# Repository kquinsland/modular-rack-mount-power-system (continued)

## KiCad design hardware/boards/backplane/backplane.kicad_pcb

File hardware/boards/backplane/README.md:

# Consolidated backplane

This directory contains the finalized Generation-2 backplane:
`backplane.kicad_pro`, `backplane.kicad_sch`, `backplane.kicad_pcb`, and
`backplane.kicad_dru`.

The PCB in this directory is the mechanical authority for the board
outline, airflow cutouts, mounting holes, and six slot-connector footprints and
placement. The carrier is the electrical authority for circuitry shared between
the two boards, including the slot pinout, STM32, CAN transceiver, current
sensor, and slot connector pinout.

## Implemented schematic

The root schematic is divided into five sheets:

- `01_power_input.kicad_sch`: DC input, 1 mOhm high-side current shunt,
  INA237 monitor;
- `02_control.kicad_sch`: STM32C092GCU6, reset/decoupling, SWD, and test points;
- `03_can_slots.kicad_sch`: TCAN3413 CAN-FD interface, external CAN protection,
  optional termination, and the six carrier slots;
- `04_fan_status.kicad_sch`: two independent 3-wire fan supply-PWM switches and
  tachometer inputs, plus an externally powered DS18B20 interface. Per-slot
  addressable LEDs were removed to keep automated assembly on one side of the
  PCB; and
- `05_buck_converters.kicad_sch`: separate LM5164 3.3 V and 12 V converters.

The Rust `backplane-firmware` target implements this board. Earlier firmware
targets and their hardware assumptions are not supported.

Both regulators use LM5164DDAR, LCSC C477928, with
PSPMAA0805-101M-ANP 100 uH inductors, LCSC C2962892. The output-specific
feedback, on-time, ripple-injection, and capacitor networks remain separate.

The PCB stackup specifies 2 oz outer copper, 1 oz inner copper, and an ENIG
surface finish.

Generate the backplane BOM, placement file, Gerber/drill archive, IPC-D-356
netlist, designator inventory, and validation manifest with
`mise run production:backplane`. A successful export records warnings in the
manifest; it does not by itself supersede the fabrication-readiness status
below.

The local I2C2 bus uses STM32 PA6/PA7 and exists only between the STM32 and
INA237. Carrier communication is CAN-FD.

## Connectors

`J8` is the main DC input:

1. GND
2. VIN_RAW

`J7` is a XINLAIYA XY308-2.54-3P three-position screw terminal, LCSC
`C557686`:

1. GND
2. CANL
3. CANH

`J7` is intentionally marked DNP and excluded from pick-and-place output because
the user installs it by hand after assembly. D1 and L3 protect only this external
CAN boundary. Each carrier has its own connector-side CAN protection, so the
backplane does not duplicate ESD parts at every slot. `SJ1` and `R17` provide
normally-open 120 ohm termination for use only when this backplane is at a
physical bus end.

`J8` is likewise marked DNP and excluded from pick-and-place output for hand
installation after assembly.

The six carrier slots retain the authoritative combined XT30 plus two-signal
footprint. Their physical pinout is:

1. VIN_BUS — power contact furthest from the two low-voltage signal contacts
2. GND — power contact between pin 1 and the two low-voltage signal contacts
3. CANH
4. CANL

The slot references are `J1` through `J6`, from slot 1 through slot 6. `J9` and
`J11` are independently controlled 3-wire fan connections: GND, switched 12 V,
and tach.

CAN differential nets use KiCad's `_P`/`_N` naming convention on both sides of
the common-mode choke: `CAN_BUS_P`/`CAN_BUS_N` and
`CAN_EXT_P`/`CAN_EXT_N`, with `P = CANH` and `N = CANL`. Custom DRC rules
enforce a 0.20-0.30 mm gap on coupled routes and a 35 mm maximum uncoupled
length. Narrowly scoped breakout areas permit up to 2.40 mm pair spacing at
connector, choke, and transceiver fan-outs. Whole-net skew is intentionally not
constrained because the six-drop `CAN_BUS` trunk is branched; aggregate P/N net
lengths do not describe a meaningful point-to-point signal path.

`J12` is the externally powered DS18B20 header:

1. GND
2. DQ (`DS18B20_DATA`, pulled up to 3.3 V through `R24`)
3. +3V3

The DS18B20 data signal uses STM32 `PA15`. The local status NeoPixel uses `PA1`
through a 100 ohm series resistor and has a dedicated 100 nF bypass capacitor.
Fan 0 uses `PA2` for supply PWM and `PB8` for tach capture. Fan 1 uses `PA0` for
supply PWM and `PA8` for tach capture.

## Power assumptions

The backplane is designed for a **24–48 V nominal system**, compatible with
24 V and future 48 V carrier generations. The current SW3538 carrier is the
limiting factor: **24 V nominal, 30 V maximum input**. A second-generation
carrier with a suitably rated module and protection is required for 48 V use.
Slot feeds are unswitched and do not provide voltage conversion; never connect
a 48 V supply while any current-generation carrier is fitted. No nominal
backplane voltage below 24 V is specified. Supply tolerance, harness drop,
startup, fault protection, and thermal performance remain qualification items.

The first population targets a nominal 24 V input and up to 100 W output per
slot. Six fully loaded slots produce a working input budget of approximately
30 A. `RSH1` is 1 mOhm, giving 30 mV and 0.9 W at 30 A; configure the INA237 for
its narrow shunt range and route the sense pair as true Kelvin connections.

The later design goal is 48 V nominal with a new carrier revision and up to
240 W per slot.
That is a future characterization target, not a released rating, until the
input-protection, current-path, thermal, transient, and first-article tests are
complete.

Both fan channels share the LM5164 12 V rail. Its combined continuous,
startup, and stall load must be tested with the intended pair of fans; adding a
second connector does not increase the regulator's 1 A output rating.

## PCB status

The schematic is synchronized into a fully placed and routed PCB. The finalized
design passes ERC and PCB DRC. Its operating limits remain conditional on the
first-article validation below.

Before ordering and assigning a production current rating:

- verify the mirrored `J1`-`J6` mating geometry, power polarity, and CANH/CANL
  ordering against a carrier;
- confirm the hand-installed `J7`, `J8`, `J9`, `J11`, and `J12` footprints and
  entry directions against the sourced parts;
- review the generated BOM, placement, Gerber, drill, and validation files; and
- perform first-article high-current, thermal, fan startup/stall, CAN-FD, and
  protection testing under the intended enclosure and airflow conditions.

See `../../../docs/interfaces.md`, `../../../docs/system-overview.md`, and
`../../../docs/power-budget.md` for the system-level definitions.

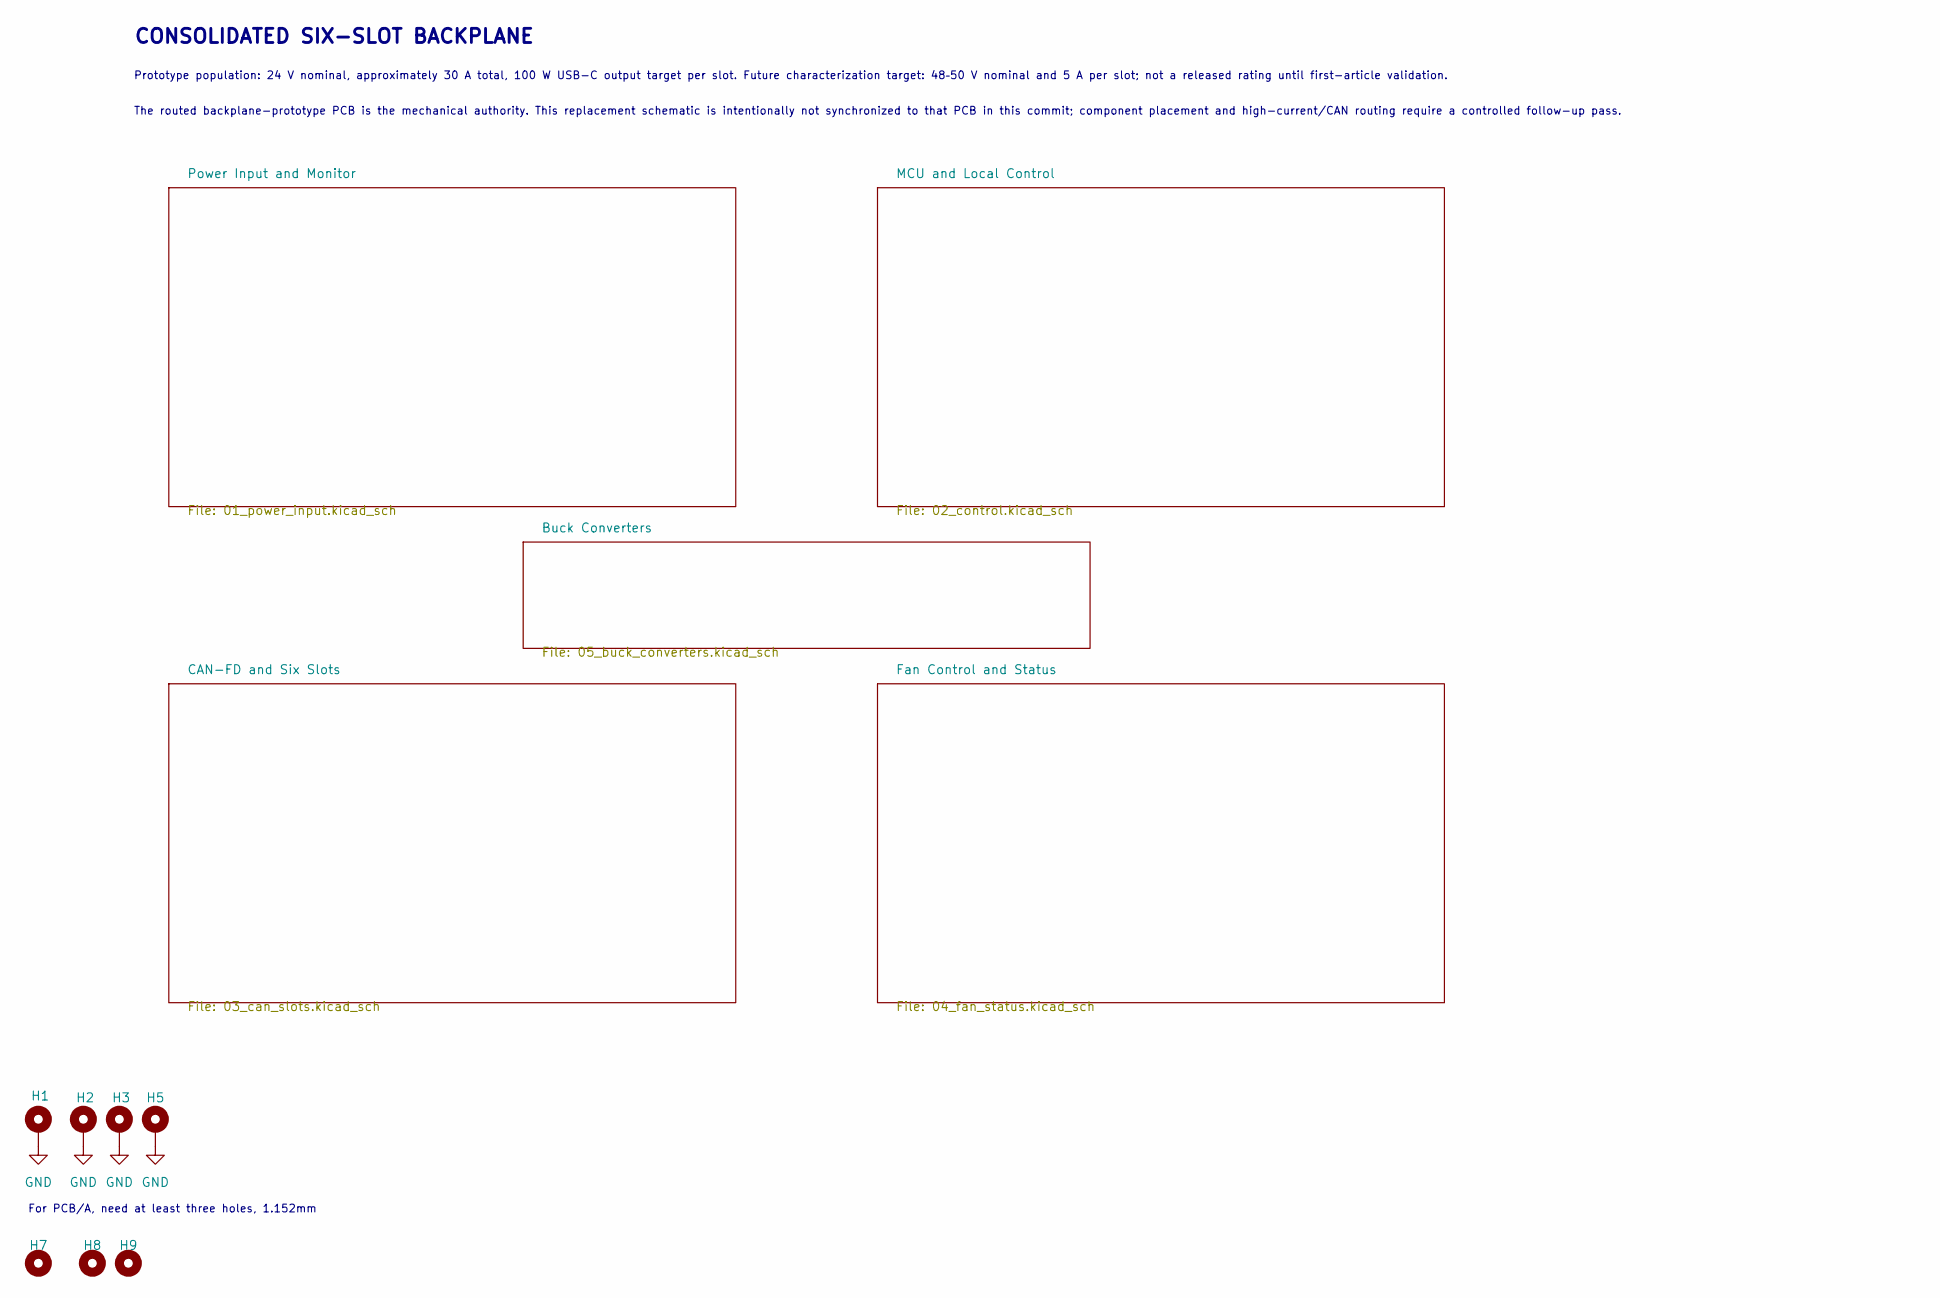
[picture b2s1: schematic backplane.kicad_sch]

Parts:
H1, H2, H3, H5: M2 CHASSIS; MountingHole_2.2mm_M2_Pad_Via_JLC
H7, H8, H9: ToolingHole_1.152mm; MountingHole_JLCPCB_Tooling_1.152mm

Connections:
GND: H1.1 (1_1), H2.1 (1_1), H3.1 (1_1), H5.1 (1_1); also elsewhere on the board

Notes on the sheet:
The routed backplane-prototype PCB is the mechanical authority. This replacement schematic is intentionally not synchronized to that PCB in this commit; component placement and high-current/CAN routing require a controlled follow-up pass.
Prototype population: 24 V nominal, approximately 30 A total, 100 W USB-C output target per slot. Future characterization target: 48–50 V nominal and 5 A per slot; not a released rating until first-article validation.
CONSOLIDATED SIX-SLOT BACKPLANE
For PCB/A, need at least three holes, 1.152mm

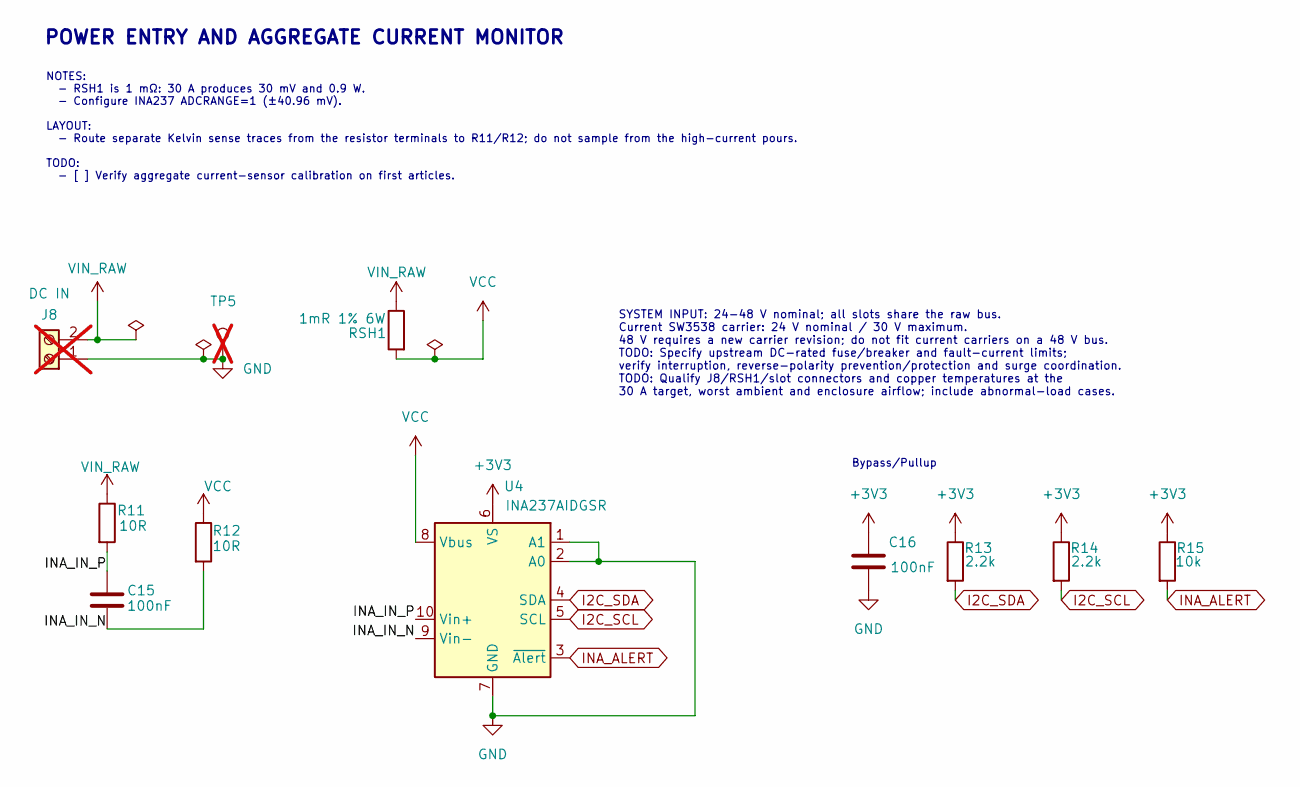
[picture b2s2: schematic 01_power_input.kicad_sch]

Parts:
C15, C16: 100nF; C_0603_1608Metric; Voltage 50 V; MPN CC0603KRX7R9BB104; LCSC C14663
J8: DC IN; DORABO_DB910-6.35-2P-GN-S; MPN DB910-6.35-2P-GN-S; LCSC C395872; not fitted
R11, R12: 10R; R_0603_1608Metric; Tolerance 1%; MPN 0603WAF100JT5E; LCSC C22859
R13, R14: 2.2k; R_0603_1608Metric; Tolerance 1%; MPN 0603WAF2201T5E; LCSC C4190
R15: 10k; R_0603_1608Metric; Tolerance 1%; MPN 0603WAF1002T5E; LCSC C25804
RSH1: 1mR 1% 6W; R_2512_6332Metric; Tolerance 1%; MPN HoLSX2512-6W-1mR-1%; LCSC C19270875
TP5: GND; TestPoint_Pad_D1.5mm; not fitted
U4: INA237AIDGSR; MSOP-10_3x3mm_P0.5mm_0.20mm_Clearance; MPN INA237AIDGSR; LCSC C2864837

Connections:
+3V3: C16.1, R13.1, R14.1, R15.1, U4.6 (VS); also elsewhere on the board
/Power Input and Monitor/INA_IN_N: C15.2, R12.2, U4.9 (Vin-)
/Power Input and Monitor/INA_IN_P: C15.1, R11.2, U4.10 (Vin+)
GND: C16.2, J8.1, TP5.1 (1_1), U4.1 (A1), U4.2 (A0), U4.7 (GND); also elsewhere on the board
I2C_SCL: R14.2, U4.5 (SCL); also elsewhere on the board
I2C_SDA: R13.2, U4.4 (SDA); also elsewhere on the board
INA_ALERT: R15.2, U4.3 (~Alert); also elsewhere on the board
VCC: R12.1, RSH1.2, U4.8 (Vbus); also elsewhere on the board
VIN_RAW: J8.2, R11.1, RSH1.1

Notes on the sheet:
NOTES: - RSH1 is 1 mΩ: 30 A produces 30 mV and 0.9 W. - Configure INA237 ADCRANGE=1 (±40.96 mV). LAYOUT: - Route separate Kelvin sense traces from the resistor terminals to R11/R12; do not sample from the high-current pours. TODO: - [ ] Verify aggregate current-sensor calibration on first articles.
Bypass/Pullup
SYSTEM INPUT: 24-48 V nominal; all slots share the raw bus. Current SW3538 carrier: 24 V nominal / 30 V maximum. 48 V requires a new carrier revision; do not fit current carriers on a 48 V bus. TODO: Specify upstream DC-rated fuse/breaker and fault-current limits; verify interruption, reverse-polar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
POWER ENTRY AND AGGREGATE CURRENT MONITOR

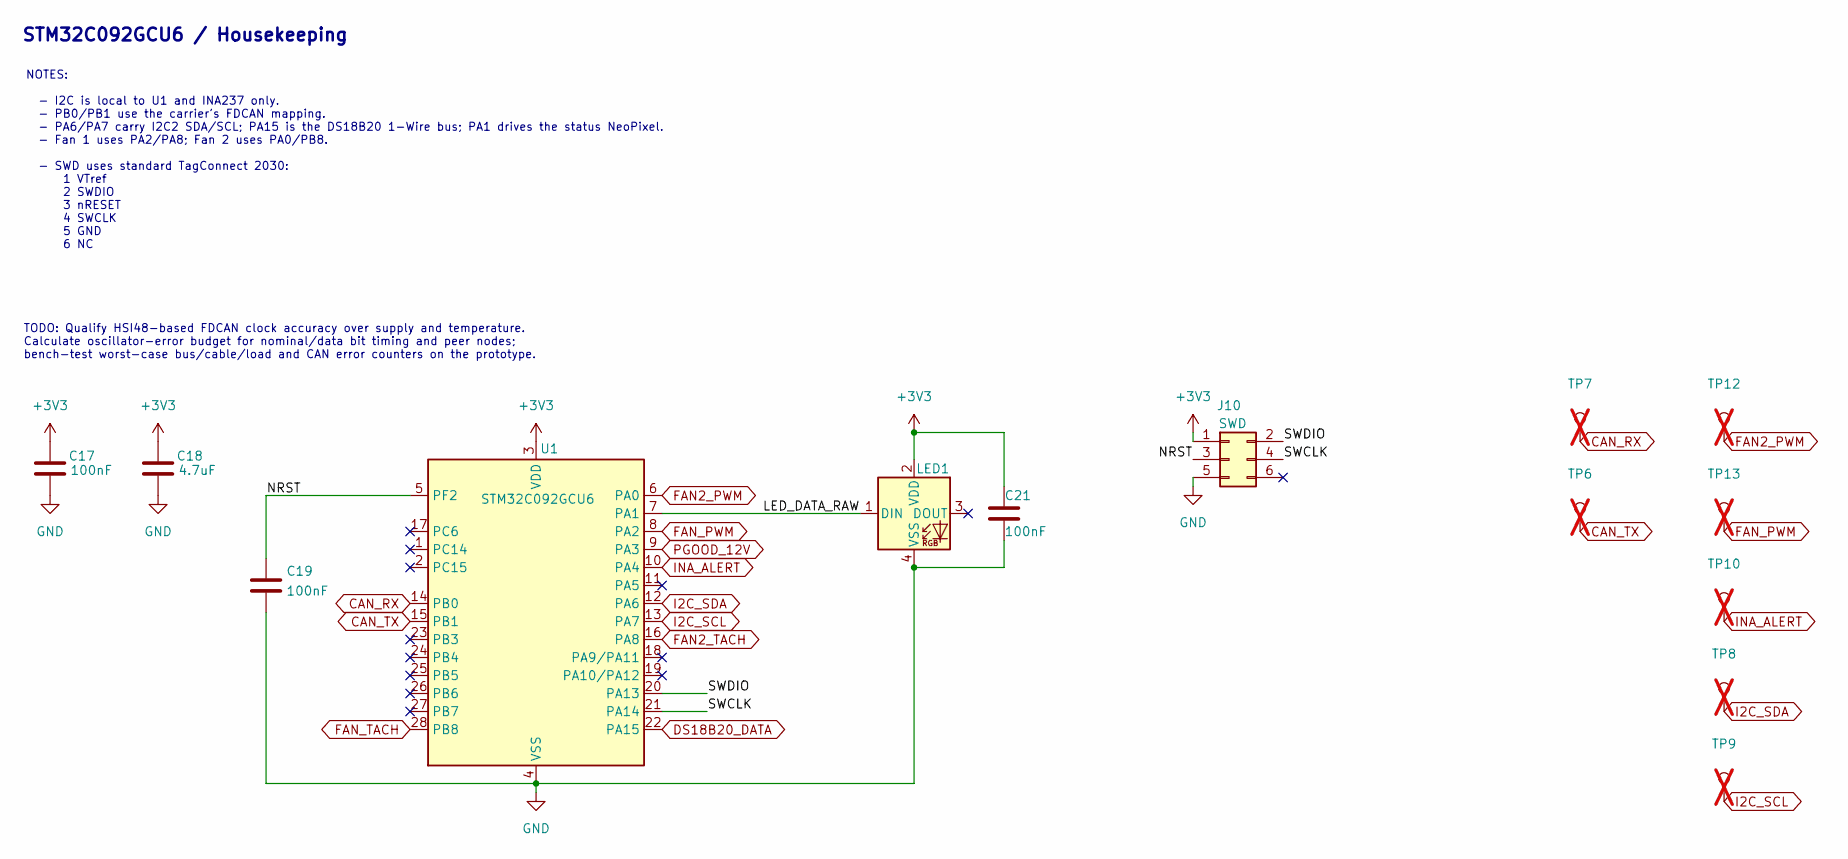
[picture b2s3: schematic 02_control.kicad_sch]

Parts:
C17, C19: 100nF; C_0603_1608Metric; Voltage 50 V; MPN CC0603KRX7R9BB104; LCSC C14663
C18: 4.7uF; C_0603_1608Metric; Voltage 10 V or greater; MPN CL10A475KO8NNNC; LCSC C19666
C21: 100nF; C_0603_1608Metric; MPN CC0603KRX7R9BB104; LCSC C14663
J10: SWD; Tag-Connect_TC2030-IDC-NL_2x03_P1.27mm_Vertical; MPN TC2030-IDC-NL
LED1: WS2812B-4020-V6; LED_Worldsemi_WS2812B-4020-V6_SideView; MPN WS2812B-4020-V6; LCSC C52941387
TP6: CAN_TX; TestPoint_Pad_D1.5mm; not fitted
TP7: CAN_RX; TestPoint_Pad_D1.5mm; not fitted
TP8: I2C_SDA; TestPoint_Pad_D1.5mm; not fitted
TP9: I2C_SCL; TestPoint_Pad_D1.5mm; not fitted
TP10: INA_ALERT; TestPoint_Pad_D1.5mm; not fitted
TP12, TP13: FAN_PWM; TestPoint_Pad_D1.5mm; not fitted
U1: STM32C092GCU6; QFN-28_4x4mm_P0.5mm; MPN STM32C092GCU6; LCSC C44847705

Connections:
+3V3: C17.1, C18.1, C21.1, J10.1, LED1.2 (VDD), U1.3 (VDD); also elsewhere on the board
/MCU and Local Control/LED_DATA_RAW: LED1.1 (DIN), U1.7 (PA1)
/MCU and Local Control/NRST: C19.1, J10.3, U1.5 (PF2)
/MCU and Local Control/SWCLK: J10.4, U1.21 (PA14)
/MCU and Local Control/SWDIO: J10.2, U1.20 (PA13)
CAN_RX: TP7.1 (1_1), U1.14 (PB0); also elsewhere on the board
CAN_TX: TP6.1 (1_1), U1.15 (PB1); also elsewhere on the board
DS18B20_DATA: U1.22 (PA15); also elsewhere on the board
FAN2_PWM: TP12.1 (1_1), U1.6 (PA0); also elsewhere on the board
FAN2_TACH: U1.16 (PA8); also elsewhere on the board
FAN_PWM: TP13.1 (1_1), U1.8 (PA2); also elsewhere on the board
FAN_TACH: U1.28 (PB8); also elsewhere on the board
GND: C17.2, C18.2, C19.2, C21.2, J10.5, LED1.4 (VSS), U1.4 (VSS); also elsewhere on the board
I2C_SCL: TP9.1 (1_1), U1.13 (PA7); also elsewhere on the board
I2C_SDA: TP8.1 (1_1), U1.12 (PA6); also elsewhere on the board
INA_ALERT: TP10.1 (1_1), U1.10 (PA4); also elsewhere on the board
PGOOD_12V: U1.9 (PA3); also elsewhere on the board

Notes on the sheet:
TODO: Qualify HSI48-based FDCAN clock accuracy over supply and temperature. Calculate oscillator-error budget for nominal/data bit timing and peer nodes; bench-test worst-case bus/cable/load and CAN error counters on the prototype.
STM32C092GCU6 / Housekeeping
NOTES: - I2C is local to U1 and INA237 only. - PB0/PB1 use the carrier's FDCAN mapping. - PA6/PA7 carry I2C2 SDA/SCL; PA15 is the DS18B20 1-Wire bus; PA1 drives the status NeoPixel. - Fan 1 uses PA2/PA8; Fan 2 uses PA0/PB8. - SWD uses standard TagConnect 2030: 1 VTref 2 SWDIO 3 nRESET 4 SWCLK 5 GND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

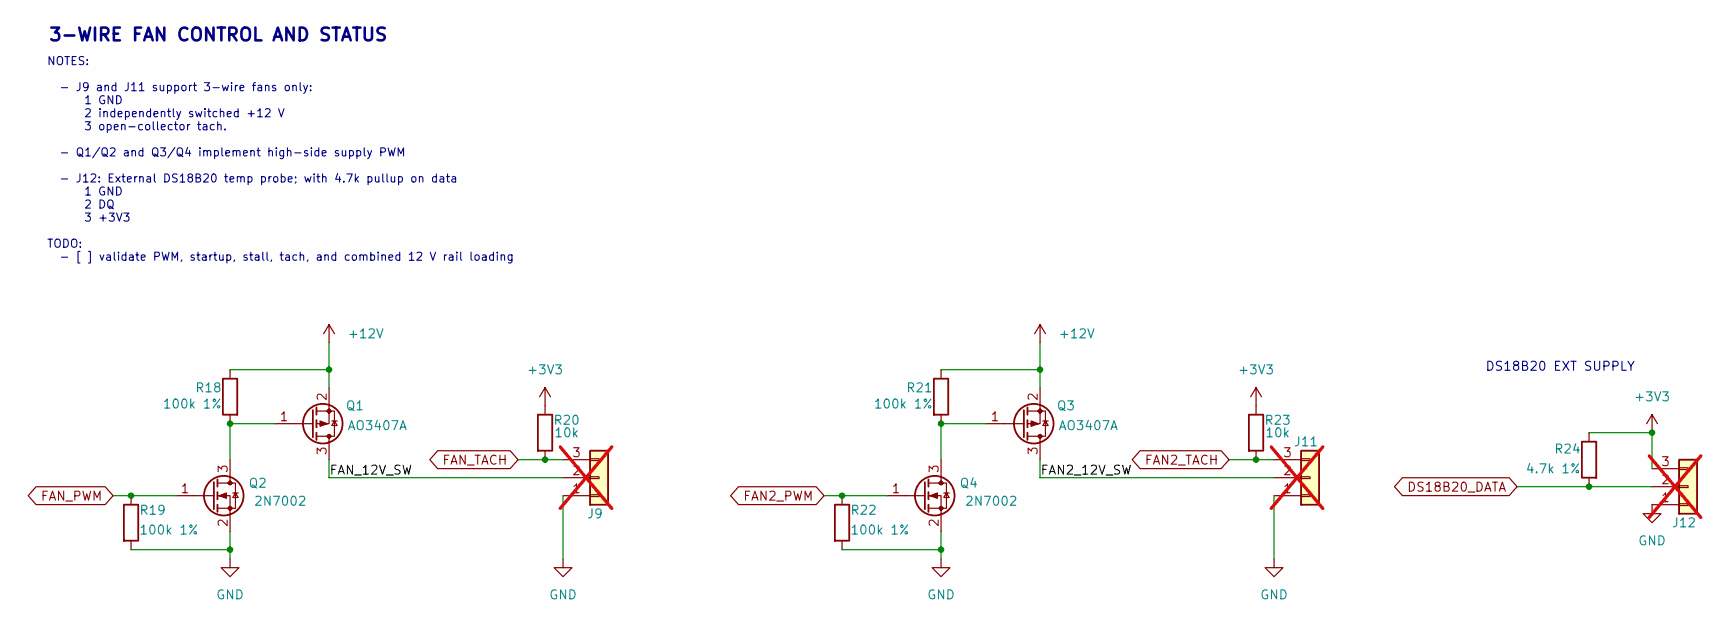
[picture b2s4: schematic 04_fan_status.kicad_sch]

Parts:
J9, J11: 12V 3-WIRE FAN; FanPinHeader_1x03_P2.54mm_Vertical_JLC_Edge; MPN TBD / user fan header; not fitted
J12: DS18B20 EXT SUPPLY; PinHeader_1x03_P2.54mm_Vertical; MPN TBD / user pin header; not fitted
Q1, Q3: AO3407A; SOT-23; MPN AO3407A; LCSC C15155
Q2, Q4: 2N7002; SOT-23; MPN 2N7002; LCSC C8545
R18, R19, R21, R22: 100k 1%; R_0603_1608Metric; Tolerance 1%; MPN 0603WAF1003T5E; LCSC C25803
R20, R23: 10k; R_0603_1608Metric; Tolerance 1%; MPN 0603WAF1002T5E; LCSC C25804
R24: 4.7k 1%; R_0603_1608Metric; Tolerance 1%; MPN 0603WAF4701T5E; LCSC C23162

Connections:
+3V3: J12.3, R20.1, R23.1, R24.1; also elsewhere on the board
+12V: Q1.2 (S), Q3.2 (S), R18.1, R21.1; also elsewhere on the board
/Fan Control and Status/FAN2_12V_SW: J11.2, Q3.3 (D)
/Fan Control and Status/FAN_12V_SW: J9.2, Q1.3 (D)
DS18B20_DATA: J12.2, R24.2; also elsewhere on the board
FAN2_PWM: Q4.1 (G), R22.1; also elsewhere on the board
FAN2_TACH: J11.3, R23.2; also elsewhere on the board
FAN_PWM: Q2.1 (G), R19.1; also elsewhere on the board
FAN_TACH: J9.3, R20.2; also elsewhere on the board
GND: J9.1, J11.1, J12.1, Q2.2 (S), Q4.2 (S), R19.2, R22.2; also elsewhere on the board
unnamed: Q1.1 (G), Q2.3 (D), R18.2
unnamed: Q3.1 (G), Q4.3 (D), R21.2

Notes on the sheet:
NOTES: - J9 and J11 support 3-wire fans only: 1 GND 2 independently switched +12 V 3 open-collector tach. - Q1/Q2 and Q3/Q4 implement high-side supply PWM - J12: External DS18B20 temp probe; with 4.7k pullup on data 1 GND 2 DQ 3 +3V3 TODO: - [ ] validate PWM, startup, stall, tach, and combined 12 V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
3-WIRE FAN CONTROL AND STATUS
DS18B20 EXT SUPPLY

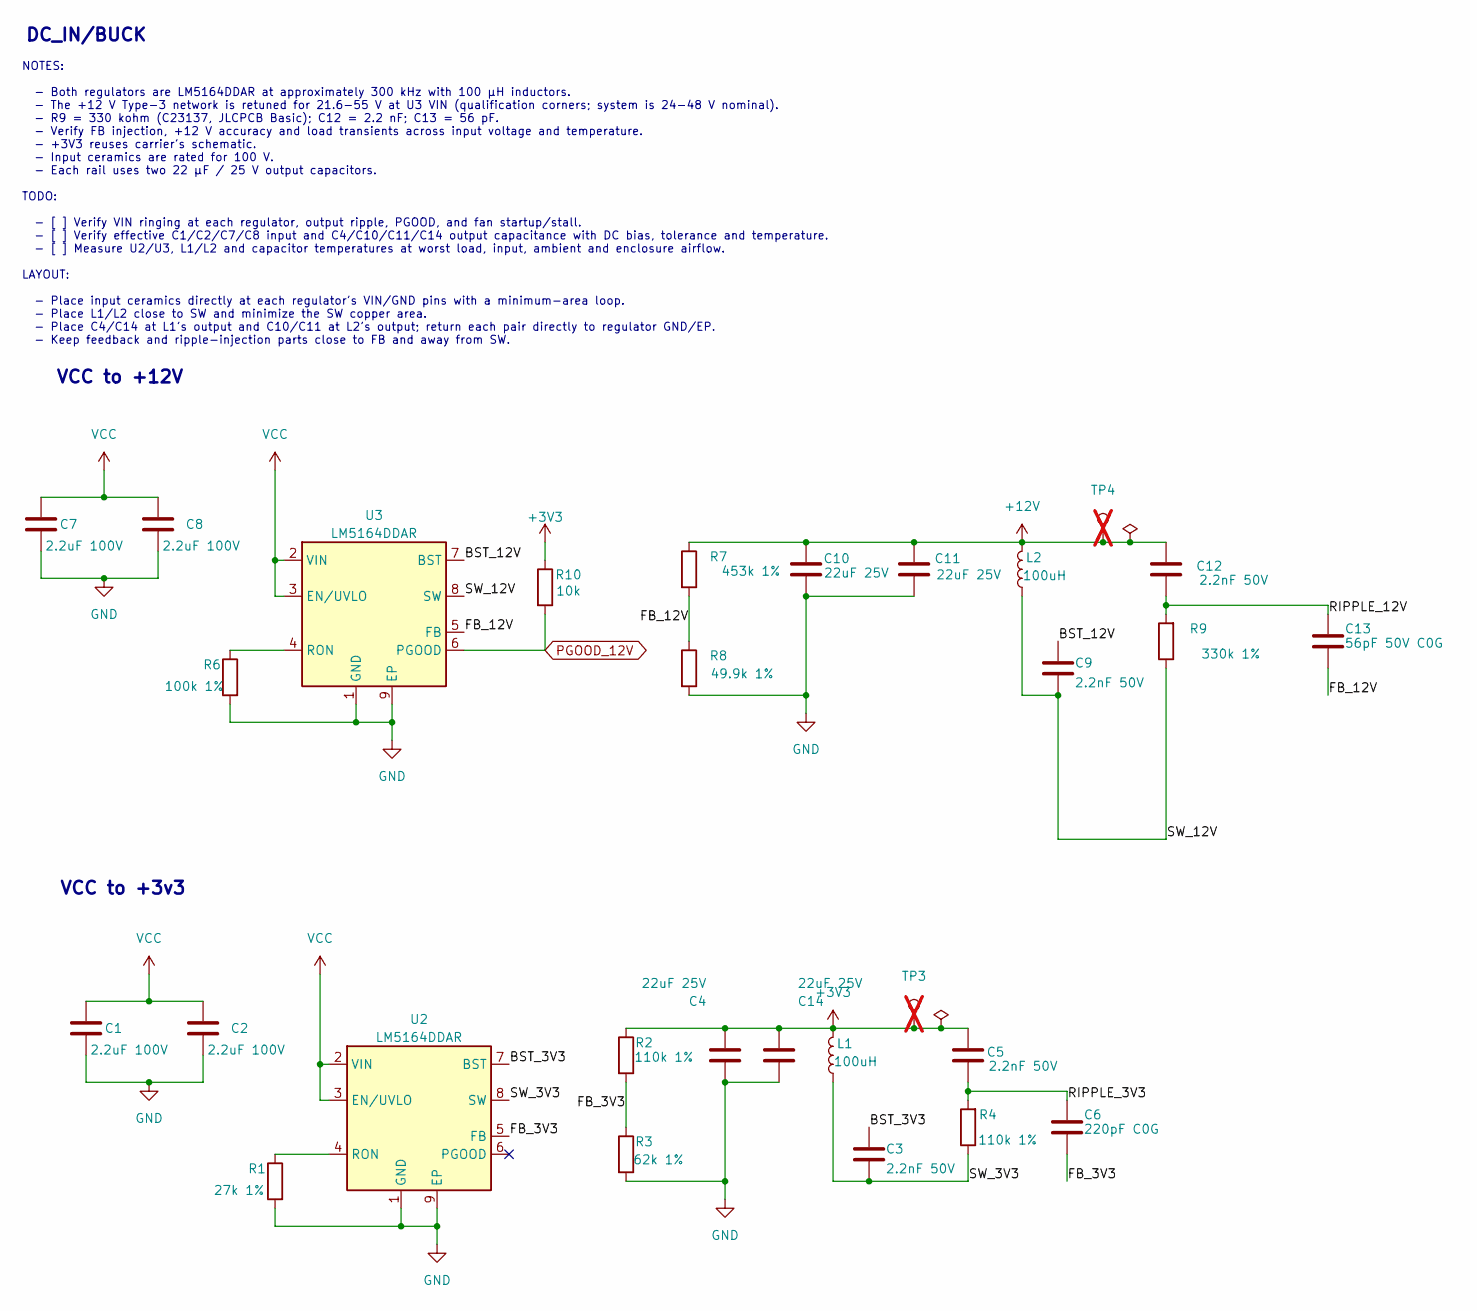
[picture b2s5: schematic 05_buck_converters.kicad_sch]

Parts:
C1, C2, C7, C8: 2.2uF 100V; C_1210_3225Metric; Voltage 100 V; MPN CL32B225KCJSNNE; LCSC C55151
C3, C5, C9, C12: 2.2nF 50V; C_0603_1608Metric; Voltage 50 V; MPN 0603B222K500NT; LCSC C1604
C4, C10, C11, C14: 22uF 25V; C_0805_2012Metric; Voltage 25 V; MPN CL21A226MAQNNNE; LCSC C45783
C6: 220pF C0G; C_0603_1608Metric; Voltage 50 V; MPN CC0603JRNPO9BN221; LCSC C106210
C13: 56pF 50V C0G; C_0603_1608Metric; Voltage 50 V; MPN 0603CG560J500NT; LCSC C1676
L1, L2: 100uH; L_PRODTech_PSPMAA0805; MPN PSPMAA0805-101M-ANP; LCSC C2962892
R1: 27k 1%; R_0603_1608Metric; Tolerance 1%; MPN 0603WAF2702T5E; LCSC C22967
R2, R4: 110k 1%; R_0603_1608Metric; Tolerance 1%; MPN 0603WAF1103T5E; LCSC C25805
R3: 62k 1%; R_0603_1608Metric; Tolerance 1%; MPN 0603WAF6202T5E; LCSC C23221
R6: 100k 1%; R_0603_1608Metric; Tolerance 1%; MPN 0603WAF1003T5E; LCSC C25803
R7: 453k 1%; R_0603_1608Metric; Tolerance 1%; MPN 0603WAF4533T5E; LCSC C25818
R8: 49.9k 1%; R_0603_1608Metric; Tolerance 1%; MPN 0603WAF4992T5E; LCSC C23184
R9: 330k 1%; R_0603_1608Metric; Tolerance 1%; MPN 0603WAF3303T5E; LCSC C23137
R10: 10k; R_0603_1608Metric; Tolerance 1%; MPN 0603WAF1002T5E; LCSC C25804
TP3: +3V3; TestPoint_Pad_D1.5mm; not fitted
TP4: +12V; TestPoint_Pad_D1.5mm; not fitted
U2, U3: LM5164DDAR; TI_SO-PowerPAD-8; MPN LM5164DDAR; LCSC C477928

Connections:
+3V3: C4.1, C5.2, C14.1, L1.2, R2.1, R10.1, TP3.1 (1_1); also elsewhere on the board
+12V: C10.1, C11.1, C12.2, L2.2, R7.1, TP4.1 (1_1); also elsewhere on the board
/Buck Converters/BST_3V3: C3.1, U2.7 (BST)
/Buck Converters/BST_12V: C9.1, U3.7 (BST)
/Buck Converters/FB_3V3: C6.2, R2.2, R3.1, U2.5 (FB)
/Buck Converters/FB_12V: C13.2, R7.2, R8.1, U3.5 (FB)
/Buck Converters/RIPPLE_3V3: C5.1, C6.1, R4.2
/Buck Converters/RIPPLE_12V: C12.1, C13.1, R9.2
/Buck Converters/SW_3V3: C3.2, L1.1, R4.1, U2.8 (SW)
/Buck Converters/SW_12V: C9.2, L2.1, R9.1, U3.8 (SW)
GND: C1.2, C2.2, C4.2, C7.2, C8.2, C10.2, C11.2, C14.2, R1.2, R3.2, R6.2, R8.2, U2.1 (GND), U2.9 (EP), U3.1 (GND), U3.9 (EP); also elsewhere on the board
unnamed: R1.1, U2.4 (RON)
unnamed: R6.1, U3.4 (RON)
PGOOD_12V: R10.2, U3.6 (PGOOD); also elsewhere on the board
VCC: C1.1, C2.1, C7.1, C8.1, U2.2 (VIN), U2.3 (EN/UVLO), U3.2 (VIN), U3.3 (EN/UVLO); also elsewhere on the board

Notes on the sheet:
DC_IN/BUCK
NOTES: - Both regulators are LM5164DDAR at approximately 300 kHz with 100 µH inductors. - The +12 V Type-3 network is retuned for 21.6-55 V at U3 VIN (qualification corners; system is 24-48 V nominal). - R9 = 330 kohm (C23137, JLCPCB Basic); C12 = 2.2 nF; C13 = 56 pF. - Verify FB injection, +12 V a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
VCC to +3v3
VCC to +12V

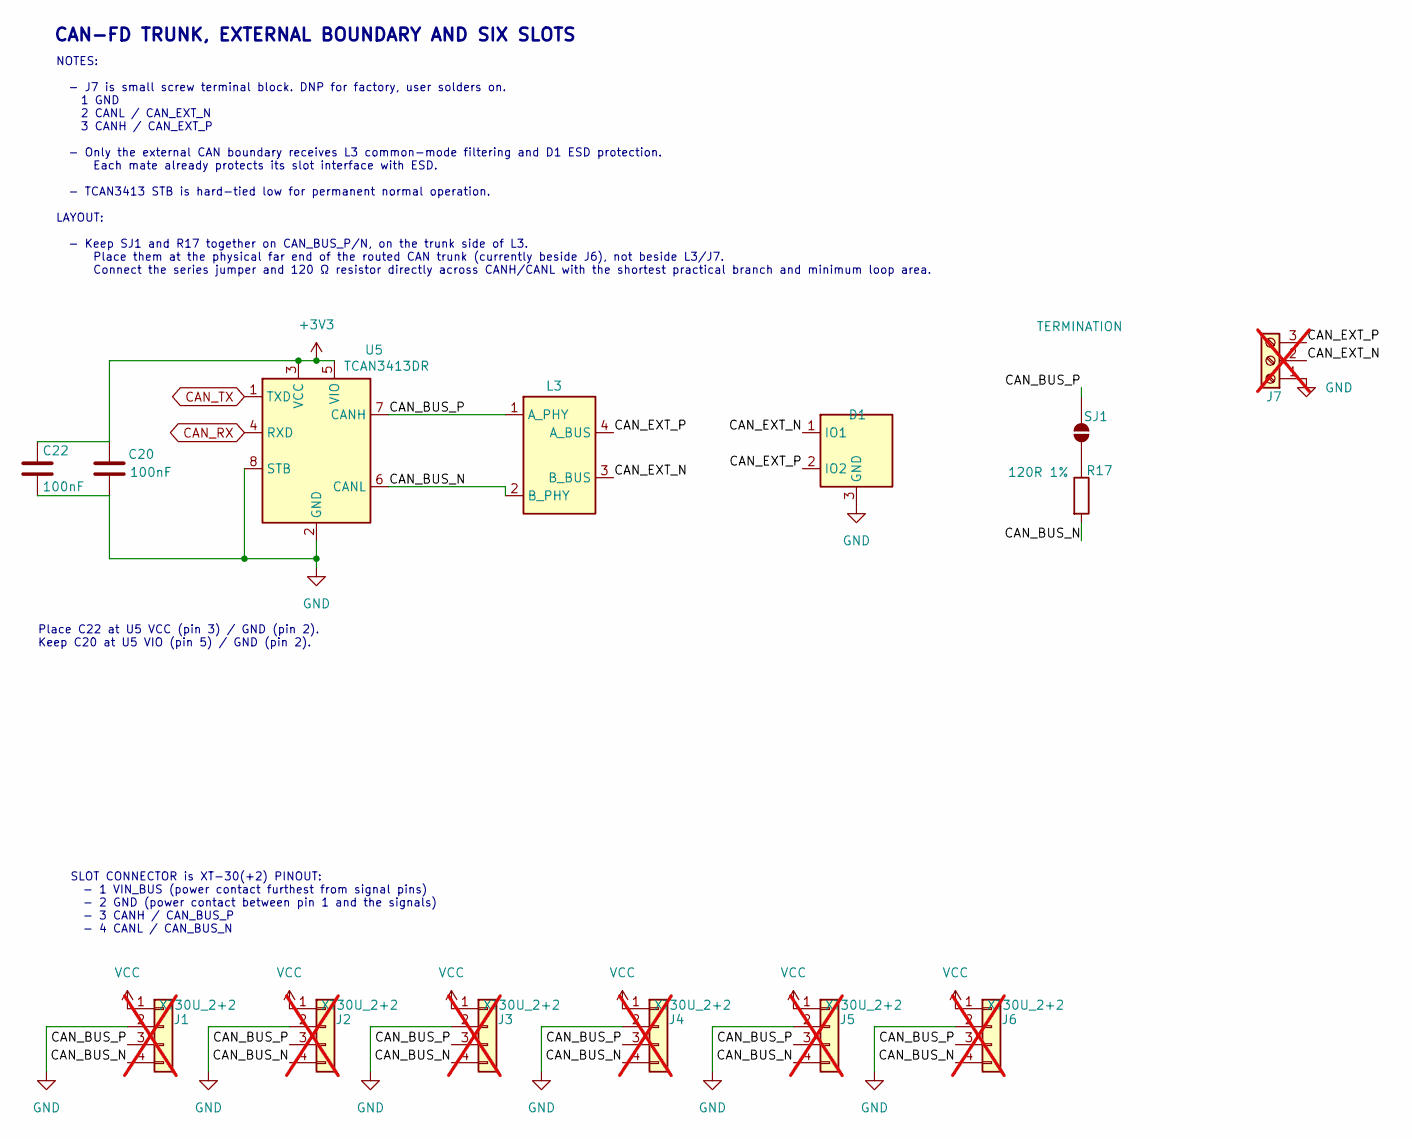
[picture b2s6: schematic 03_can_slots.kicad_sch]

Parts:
C20, C22: 100nF; C_0603_1608Metric; Voltage 50 V; MPN CC0603KRX7R9BB104; LCSC C14663
D1: PESD2CANFD27V-TR; SOT-23; MPN PESD2CANFD27V-TR; LCSC C552488
J1, J2, J3, J4, J5, J6: XT30U_2+2; Amass_XT30U_2plus2_F; MPN XT30U(2+2)-F.G.B; LCSC C30170181; not fitted
J7: XY308-2.54-3P / EXTERNAL CAN; TerminalBlock_Xinya_XY308-2.54-3P_1x03_P2.54mm_Horizontal; MPN XY308-2.54-3P; LCSC C557686; not fitted
L3: ACT1210D-101-2P-TL00; L_CommonModeChoke_TDK_ACT1210D; MPN ACT1210D-101-2P-TL00; LCSC C3039743
R17: 120R 1%; R_0603_1608Metric; Tolerance 1%; MPN 0603WAF1200T5E; LCSC C22787
SJ1: TERMINATION; SolderJumper-2_P1.3mm_Open_Pad1.0x1.5mm; MPN PCB solder jumper
U5: TCAN3413DR; SOIC-8_3.9x4.9mm_P1.27mm; MPN TCAN3413DR; LCSC C22433320

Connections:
+3V3: C20.1, C22.1, U5.3 (VCC), U5.5 (VIO); also elsewhere on the board
/CAN-FD and Six Slots/CAN_BUS_N: J1.4, J2.4, J3.4, J4.4, J5.4, J6.4, L3.2 (B_PHY), R17.2, U5.6 (CANL)
/CAN-FD and Six Slots/CAN_BUS_P: J1.3, J2.3, J3.3, J4.3, J5.3, J6.3, L3.1 (A_PHY), SJ1.1 (A), U5.7 (CANH)
/CAN-FD and Six Slots/CAN_EXT_N: D1.1 (IO1), J7.2, L3.3 (B_BUS)
/CAN-FD and Six Slots/CAN_EXT_P: D1.2 (IO2), J7.3, L3.4 (A_BUS)
CAN_RX: U5.4 (RXD); also elsewhere on the board
CAN_TX: U5.1 (TXD); also elsewhere on the board
GND: C20.2, C22.2, D1.3 (GND), J1.2, J2.2, J3.2, J4.2, J5.2, J6.2, J7.1, U5.2 (GND), U5.8 (STB); also elsewhere on the board
unnamed: R17.1, SJ1.2 (B)
VCC: J1.1, J2.1, J3.1, J4.1, J5.1, J6.1; also elsewhere on the board

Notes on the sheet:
SLOT CONNECTOR is XT-30(+2) PINOUT: - 1 VIN_BUS (power contact furthest from signal pins) - 2 GND (power contact between pin 1 and the signals) - 3 CANH / CAN_BUS_P - 4 CANL / CAN_BUS_N
NOTES: - J7 is small screw terminal block. DNP for factory, user solders on. 1 GND 2 CANL / CAN_EXT_N 3 CANH / CAN_EXT_P - Only the external CAN boundary receives L3 common-mode filtering and D1 ESD protection. Each mate already protects its slot interface with ESD. - TCAN3413 STB is hard-tied low 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
CAN-FD TRUNK, EXTERNAL BOUNDARY AND SIX SLOTS
Place C22 at U5 VCC (pin 3) / GND (pin 2). Keep C20 at U5 VIO (pin 5) / GND (pin 2).

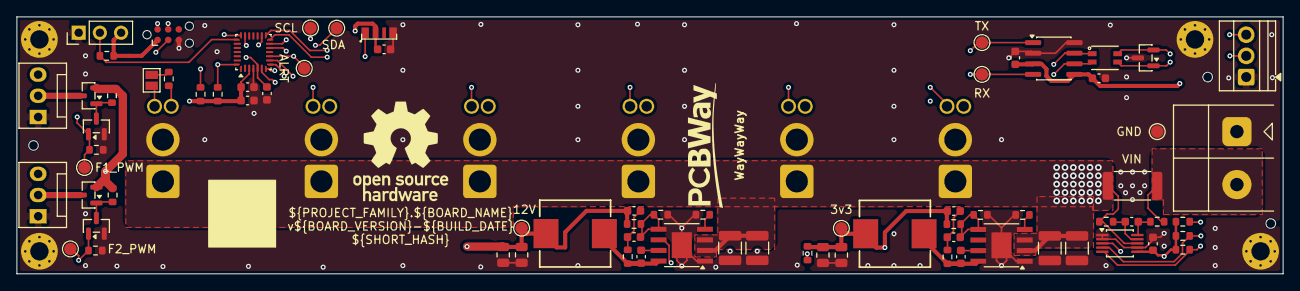
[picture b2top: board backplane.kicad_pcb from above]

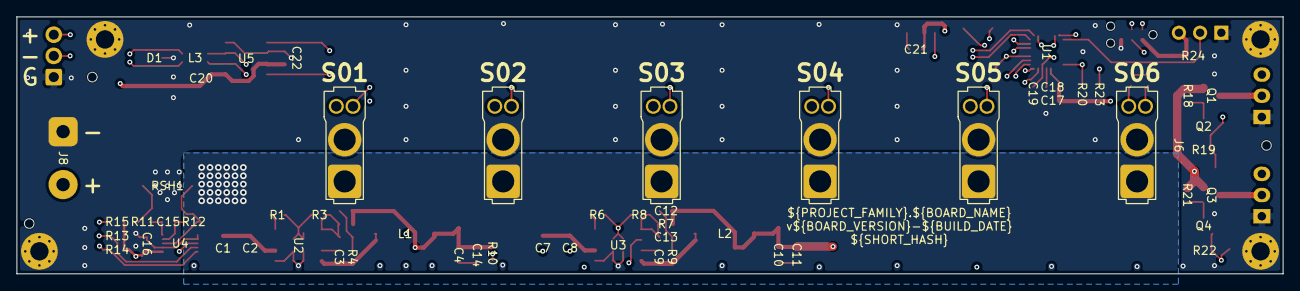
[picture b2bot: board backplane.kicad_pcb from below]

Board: 4 copper layers, 151.8 x 30.8 mm, 90 parts (10 on the bottom side), 41 nets.

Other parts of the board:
LOGO_PCBWAY: PCBWay_Logo_15mm

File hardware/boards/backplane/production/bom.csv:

Designator,Footprint,Quantity,Value,LCSC Part #
"C1, C2, C7, C8",C_1210_3225Metric,4,2.2uF 100V,C55151
"C3, C5, C9, C12",C_0603_1608Metric,4,2.2nF 50V,C1604
"C4, C10, C11, C14",C_0805_2012Metric,4,22uF 25V,C45783
C6,C_0603_1608Metric,1,220pF C0G,C106210
C13,C_0603_1608Metric,1,56pF 50V C0G,C1676
"C15, C16, C17, C19, C20, C21, C22",C_0603_1608Metric,7,100nF,C14663
C18,C_0603_1608Metric,1,4.7uF,C19666
D1,SOT-23,1,PESD2CANFD27V-TR,C552488
"L1, L2",L_PRODTech_PSPMAA0805,2,100uH,C2962892
L3,L_CommonModeChoke_TDK_ACT1210D,1,ACT1210D-101-2P-TL00,C3039743
LED1,LED_Worldsemi_WS2812B-4020-V6_SideView,1,WS2812B-4020-V6,C52941387
"Q1, Q3",SOT-23,2,AO3407A,C15155
"Q2, Q4",SOT-23,2,2N7002,C8545
R1,R_0603_1608Metric,1,27k 1%,C22967
"R2, R4",R_0603_1608Metric,2,110k 1%,C25805
R3,R_0603_1608Metric,1,62k 1%,C23221
"R6, R18, R19, R21, R22",R_0603_1608Metric,5,100k 1%,C25803
R7,R_0603_1608Metric,1,453k 1%,C25818
R8,R_0603_1608Metric,1,49.9k 1%,C23184
R9,R_0603_1608Metric,1,330k 1%,C23137
"R10, R15, R20, R23",R_0603_1608Metric,4,10k,C25804
"R11, R12",R_0603_1608Metric,2,10R,C22859
"R13, R14",R_0603_1608Metric,2,2.2k,C4190
R17,R_0603_1608Metric,1,120R 1%,C22787
R24,R_0603_1608Metric,1,4.7k 1%,C23162
RSH1,R_2512_6332Metric,1,1mR 1% 6W,C19270875
U1,QFN-28_4x4mm_P0.5mm,1,STM32C092GCU6,C44847705
"U2, U3",TI_SO-PowerPAD-8,2,LM5164DDAR,C477928
U4,MSOP-10_3x3mm_P0.5mm_0.20mm_Clearance,1,INA237AIDGSR,C2864837
U5,SOIC-8_3.9x4.9mm_P1.27mm,1,TCAN3413DR,C22433320

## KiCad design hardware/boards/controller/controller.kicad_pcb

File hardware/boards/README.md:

# Boards

Each physical PCB gets its own KiCad project directory.

Current boards:

- `backplane`
- `carrier`

Both active boards use the same STM32C092GCU6 and direct CAN-FD architecture.
The backplane and carrier directories are the only product board definitions;
earlier research layouts are not compatibility targets. Some shared library
nicknames retain their original internal name so the finalized KiCad references
remain stable.

Future boards should follow the same pattern: `hardware/boards/<board-name>/<board-name>.kicad_pro`.

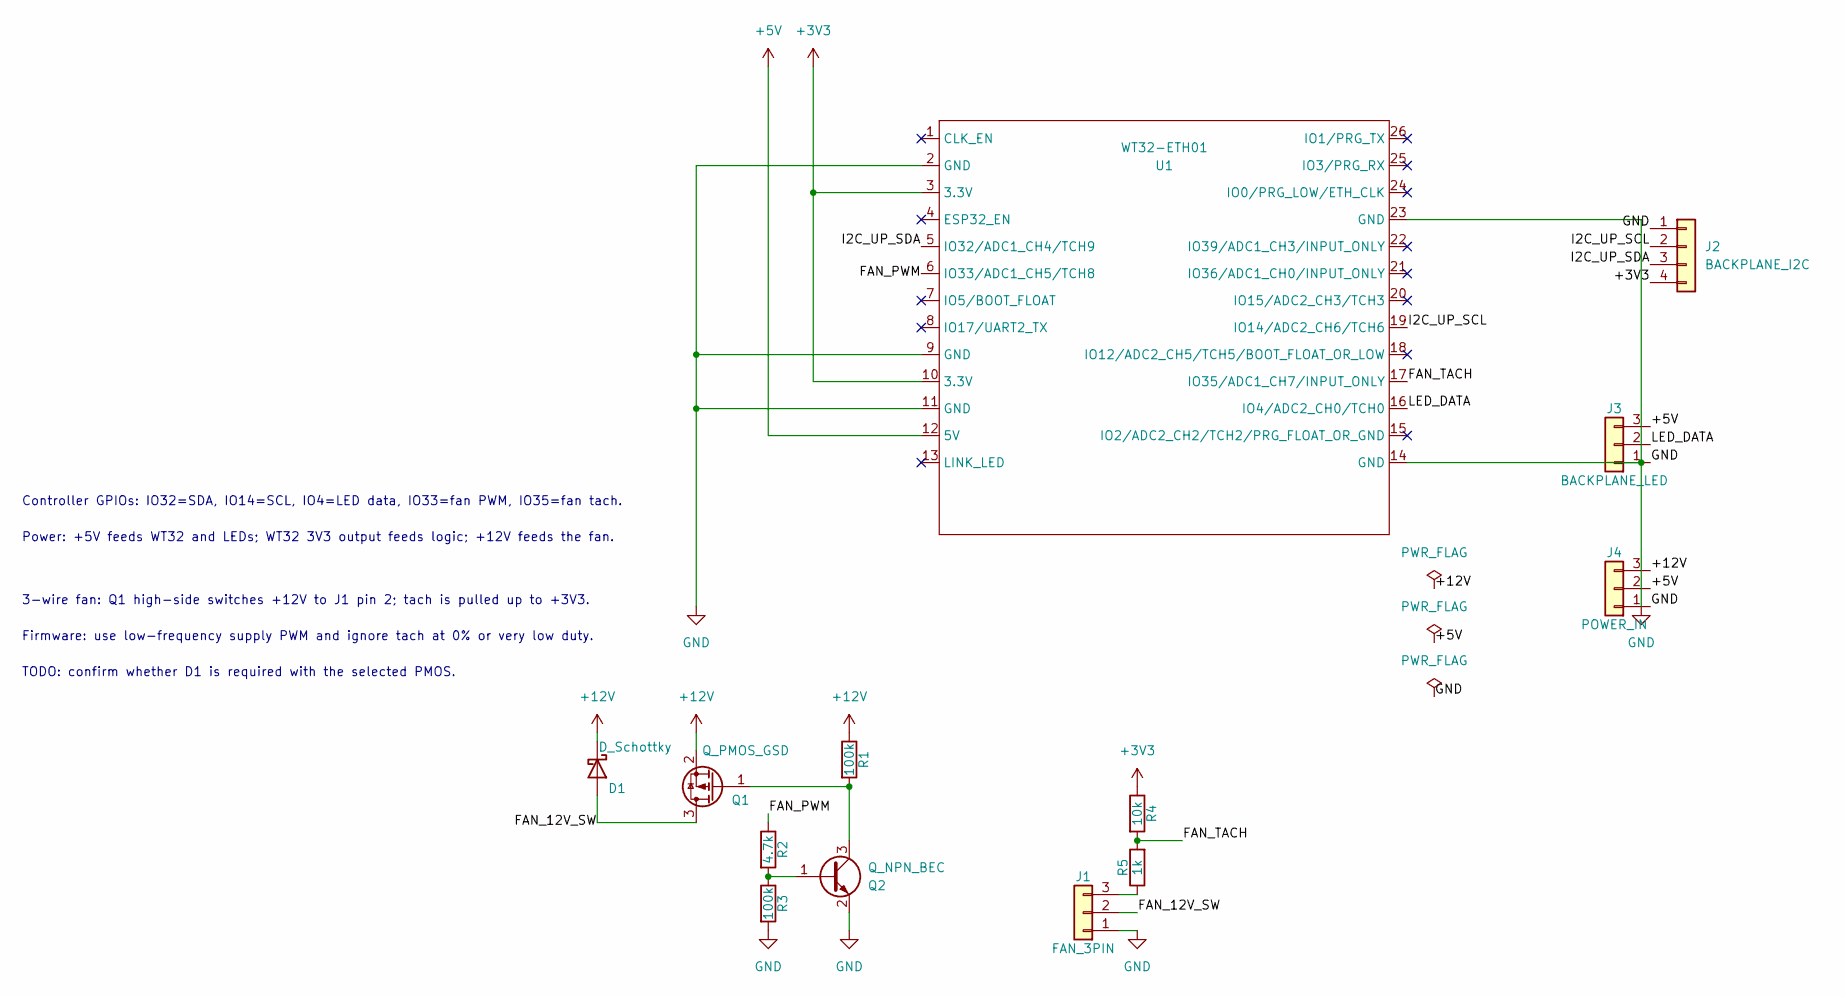
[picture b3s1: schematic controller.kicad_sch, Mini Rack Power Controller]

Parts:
D1: D_Schottky; D_SOD-123; Part_source LCSC,XXXXXXX
J1: FAN_3PIN; PinHeader_1x03_P2.54mm_Vertical; Part_source LCSC,XXXXXXX
J2: BACKPLANE_I2C; PinHeader_1x04_P2.54mm_Vertical
J3: BACKPLANE_LED; PinHeader_1x03_P2.54mm_Vertical; Part_source LCSC,XXXXXXX
J4: POWER_IN; PinHeader_1x03_P2.54mm_Vertical; Part_source LCSC,XXXXXXX
Q1: Q_PMOS_GSD; SOT-23; Part_source LCSC,XXXXXXX
Q2: Q_NPN_BEC; SOT-23; Part_source LCSC,XXXXXXX
R1, R3: 100k; R_0603_1608Metric; Part_source LCSC,XXXXXXX
R2: 4.7k; R_0603_1608Metric; Part_source LCSC,XXXXXXX
R4: 10k; R_0603_1608Metric; Part_source LCSC,XXXXXXX
R5: 1k; R_0603_1608Metric; Part_source LCSC,XXXXXXX
U1: WT32-ETH01; Part_source LCSC,XXXXXXX

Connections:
+3V3: J2.4, R4.1, U1.3 (3.3V), U1.10 (3.3V)
+5V: J3.3, J4.2, U1.12 (5V)
+12V: D1.1 (K), J4.3, Q1.2 (S), R1.1
/FAN_12V_SW: D1.2 (A), J1.2, Q1.3 (D)
/FAN_PWM: R2.1, U1.6 (IO33/ADC1_CH5/TCH8)
/FAN_TACH: R4.2, R5.2, U1.17 (IO35/ADC1_CH7/INPUT_ONLY)
/I2C_UP_SCL: J2.2, U1.19 (IO14/ADC2_CH6/TCH6)
/I2C_UP_SDA: J2.3, U1.5 (IO32/ADC1_CH4/TCH9)
/LED_DATA: J3.2, U1.16 (IO4/ADC2_CH0/TCH0)
GND: J1.1, J2.1, J3.1, J4.1, Q2.2 (E), R3.2, U1.2 (GND), U1.9 (GND), U1.11 (GND), U1.14 (GND), U1.23 (GND)
unnamed: J1.3, R5.1
unnamed: Q1.1 (G), Q2.3 (C), R1.2
unnamed: Q2.1 (B), R2.2, R3.1

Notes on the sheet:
Controller GPIOs: IO32=SDA, IO14=SCL, IO4=LED data, IO33=fan PWM, IO35=fan tach.
Power: +5V feeds WT32 and LEDs; WT32 3V3 output feeds logic; +12V feeds the fan.
3-wire fan: Q1 high-side switches +12V to J1 pin 2; tach is pulled up to +3V3.
Firmware: use low-frequency supply PWM and ignore tach at 0% or very low duty.
TODO: confirm whether D1 is required with the selected PMOS.

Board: 2 copper layers, 13 parts (0 on the bottom side), 13 nets, no tracks yet.
